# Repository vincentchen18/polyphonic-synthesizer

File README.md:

# Polyphonic Synthesizer

## Overview

You're probably wondering why this is called a polyphonic synthesizer. Well, I thought it sounded fancier than "scrappy 2 octave piano". Anyway, this is my 2nd PCB project, made for the week 3, Instruments, of the [Half Life YSWS](halflife.hackclub.com) from Hack Club.

As a former unskilled piano player (AMEB G6), I decided to make an electronic keyboard this week cos why not. :))) 

Well, at least it's supposed to be an electric keyboard. I'm pretty sure the keys are a bit smaller than they actually are supposed to be, but at least their shape is recognisable, right?

## Schematics

Above is my final schematic for the Synthesizer. As you can see, it contains a USB-C receptacle, Raspberry Pi Pico, some OLEDs, 25 switches (1 per key for 25 keys), and 8 knobs for customised sound settings.

## Hardware and assembly

This is my PCB render of my project. 

Basically, you need a bunch of Cherry MX switches that you need to stick onto the squares at the bottom. 

Then, you gotta 3D print the white and black key files in [here](3D%20Models/STLs/), ideally in PLA or PETG filament. 

Next, you need to stick the holes of the 3D printed parts onto the stems of the switches, and there should be enough tolerance to stick it in easily.

There's also a bunch of soldering that you need to do for the electrical components, but aside from that it's pretty easy.

It is also important to note that the [enclosure](3D%20Models/STLs/enclosure.stl) is completely optional, and exists only to hold the PCB so it doesn't slide around if you're trying to play it. It does not in any way affect the functionality of the actual piano.

If you do print the enclosure, please note that it is too large for a standard 3D printer with a buildspace of 220mm x 220mm x 220mm, so I have already halved the box in the STL model, and all you gotta do is either superglue the halves together or zip tie the 2 halves together using the provided 6mm diameter zip tie holes. (Zip ties are recommended)

The enclosure also has 2 holes for the USB cable and also the audio jack. Place the PCB inside it accordingly. 

You may also notice that there is absolutely no top panel or lid for the enclosure. Please note that this is **intended**. so you can see my beautiful silkscreen art and also I do not have any access to hinges :CC

## Features

I dont even have much to say here, it's just a regular piano?? If you're seeing this and you're a music student then this is a sign to go back to studying music theory.

- Optional Ear/Headphone support (there's an audio jack but you don't need to use it. unfortunately no bluetooth support :C)
- Feels like an actual electronic keyboard (cos of the keyswitches =DDD)
- Adjustable knobs (edit: im done programming firmware! :3)

| Knob | What it does                                                                             |
|---|------------------------------------------------------------------------------------------|
| **Volume** | how loud the thingy is                                                                   |
| **Instrument** | switches between 5 sounds: Piano, Organ, Pluck, Bell and 8-bit                           |
| **Tone** | makes it darker or brighter, like turning the treble down/up                             |
| **Attack** | how fast a note fades in, turn up for a swell similar to a violin                        |
| **Release** | basically a damper pedal                                                                 |
| **Echo** | adds repeating echoes                                                                    |
| **Octave** | shifts the keyboard +/- 2 octaves so you can basically get the range of the entire piano |
| **Transpose** | shifts every note +/- 6 semitones in case you get bored of your key                      |

- The OLED shows the current instrument, octave and transpose, a bar when you turn a knob, and the notes you're holding.

## 3D models

The 3d modelling was made in onshape. Find the editable model at this link: [https://cad.onshape.com/documents/eaea6aaede962270a3775490/w/8b0d608019392835e9ec1b16/e/e5c3a90dd200dcba6fe43490?renderMode=0&uiState=6adddfe965922c75c7df5742](https://cad.onshape.com/documents/eaea6aaede962270a3775490/w/8b0d608019392835e9ec1b16/e/e5c3a90dd200dcba6fe43490?renderMode=0&uiState=6adddfe965922c75c7df5742)

## Firmware

The Firmware for this project is programmed in Arduino IDE.

## AI Usage

No AI used in this project.

## Bill of Materials

### Grant-funded ($30 USD)

| Item | Purpose | Qty | Price | Source |
|---|---|---|---|---|
| Custom PCB 300×90mm, 2-layer (incl. shipping, $5 JLCONE coupon) | Main board | 5 | US$23.25 | [JLCPCB](https://jlcpcb.com) |
| USB-C receptacle HRO TYPE-C-31-M-12 | Power + USB data | 5 | US$0.87 | [LCSC](https://www.lcsc.com/product-detail/C165948.html) |
| SMAJ5.0CA TVS diode | USB ESD protection | 20 | US$0.61 | [LCSC](https://www.lcsc.com/product-detail/C908809.html) |
| SMD1206-050-16 500mA polyfuse | USB overcurrent protection | 10 | US$0.43 | [LCSC](https://www.lcsc.com/product-detail/C46641014.html) |
| Raspberry Pi Pico RP2040 (micro USB) + free knob caps (incl. GST) | Microcontroller | 1 | US$3.16 | [AliExpress](https://www.aliexpress.com/item/1005004565422217.html) |
| **Grant total** | | | **US$28.32** | |

### Paid out of pocket

| Item | Purpose                                                                              | Qty | Price | Source |
|---|--------------------------------------------------------------------------------------|---|---|---|
| Gateron G Pro 3.0 MX switches (30pc) | Keys (25 needed, 8 leftover from [Starbie](https://github.com/vincentchen18/starbie)) | 1 pack | AU$5.49 | [AliExpress](https://www.aliexpress.com/item/1005010559544082.html) |
| 1N4148 DO-35 diodes (50pc) | Key matrix anti-ghosting                                                             | 1 pack | AU$2.83 | [AliExpress](https://www.aliexpress.com/item/1005012020521505.html) |
| RV09 10K vertical potentiometers (5pc) | 8 control knobs                                                                      | 2 packs | AU$2.78 | [AliExpress](https://www.aliexpress.com/item/1871188517.html) |
| CD4051BE DIP-16 | Analog mux for the 8 knobs                                                           | 1 | AU$2.44 | [AliExpress](https://www.aliexpress.com/item/1005012399429493.html) |
| 0.96" I2C OLED 128x64 | Display                                                                              | 1 | AU$3.74 | [AliExpress](https://www.aliexpress.com/item/1005009784993412.html) |
| GY-PCM5102 I2S DAC module | Audio DAC + headphone jack                                                           | 1 | AU$4.19 | [AliExpress](https://www.aliexpress.com/item/1005005692721202.html) |
| PAM8302A CJMCU-832 amp module | Speaker amplifier                                                                    | 1 | AU$2.50 | [AliExpress](https://www.aliexpress.com/item/1005007274382818.html) |
| 8Ω 1W 28mm speaker (2pc) | Speaker                                                                              | 1 pack | AU$4.60 | [AliExpress](https://www.aliexpress.com/item/1005009051447480.html) |
| 10% GST | Tax                                                                                  | — | AU$2.86 | — |
| **Out-of-pocket total** |                                                                                      | | **AU$31.43 (US$21.98)** | |

### Already owned

| Item | Purpose | Qty |
|---|---|---|
| 10k resistors (1/4W) | USB-C CC pull-downs | 4 |

**Project total: US$50.30** *(AUD converted at AU$1 = US$0.6994)*

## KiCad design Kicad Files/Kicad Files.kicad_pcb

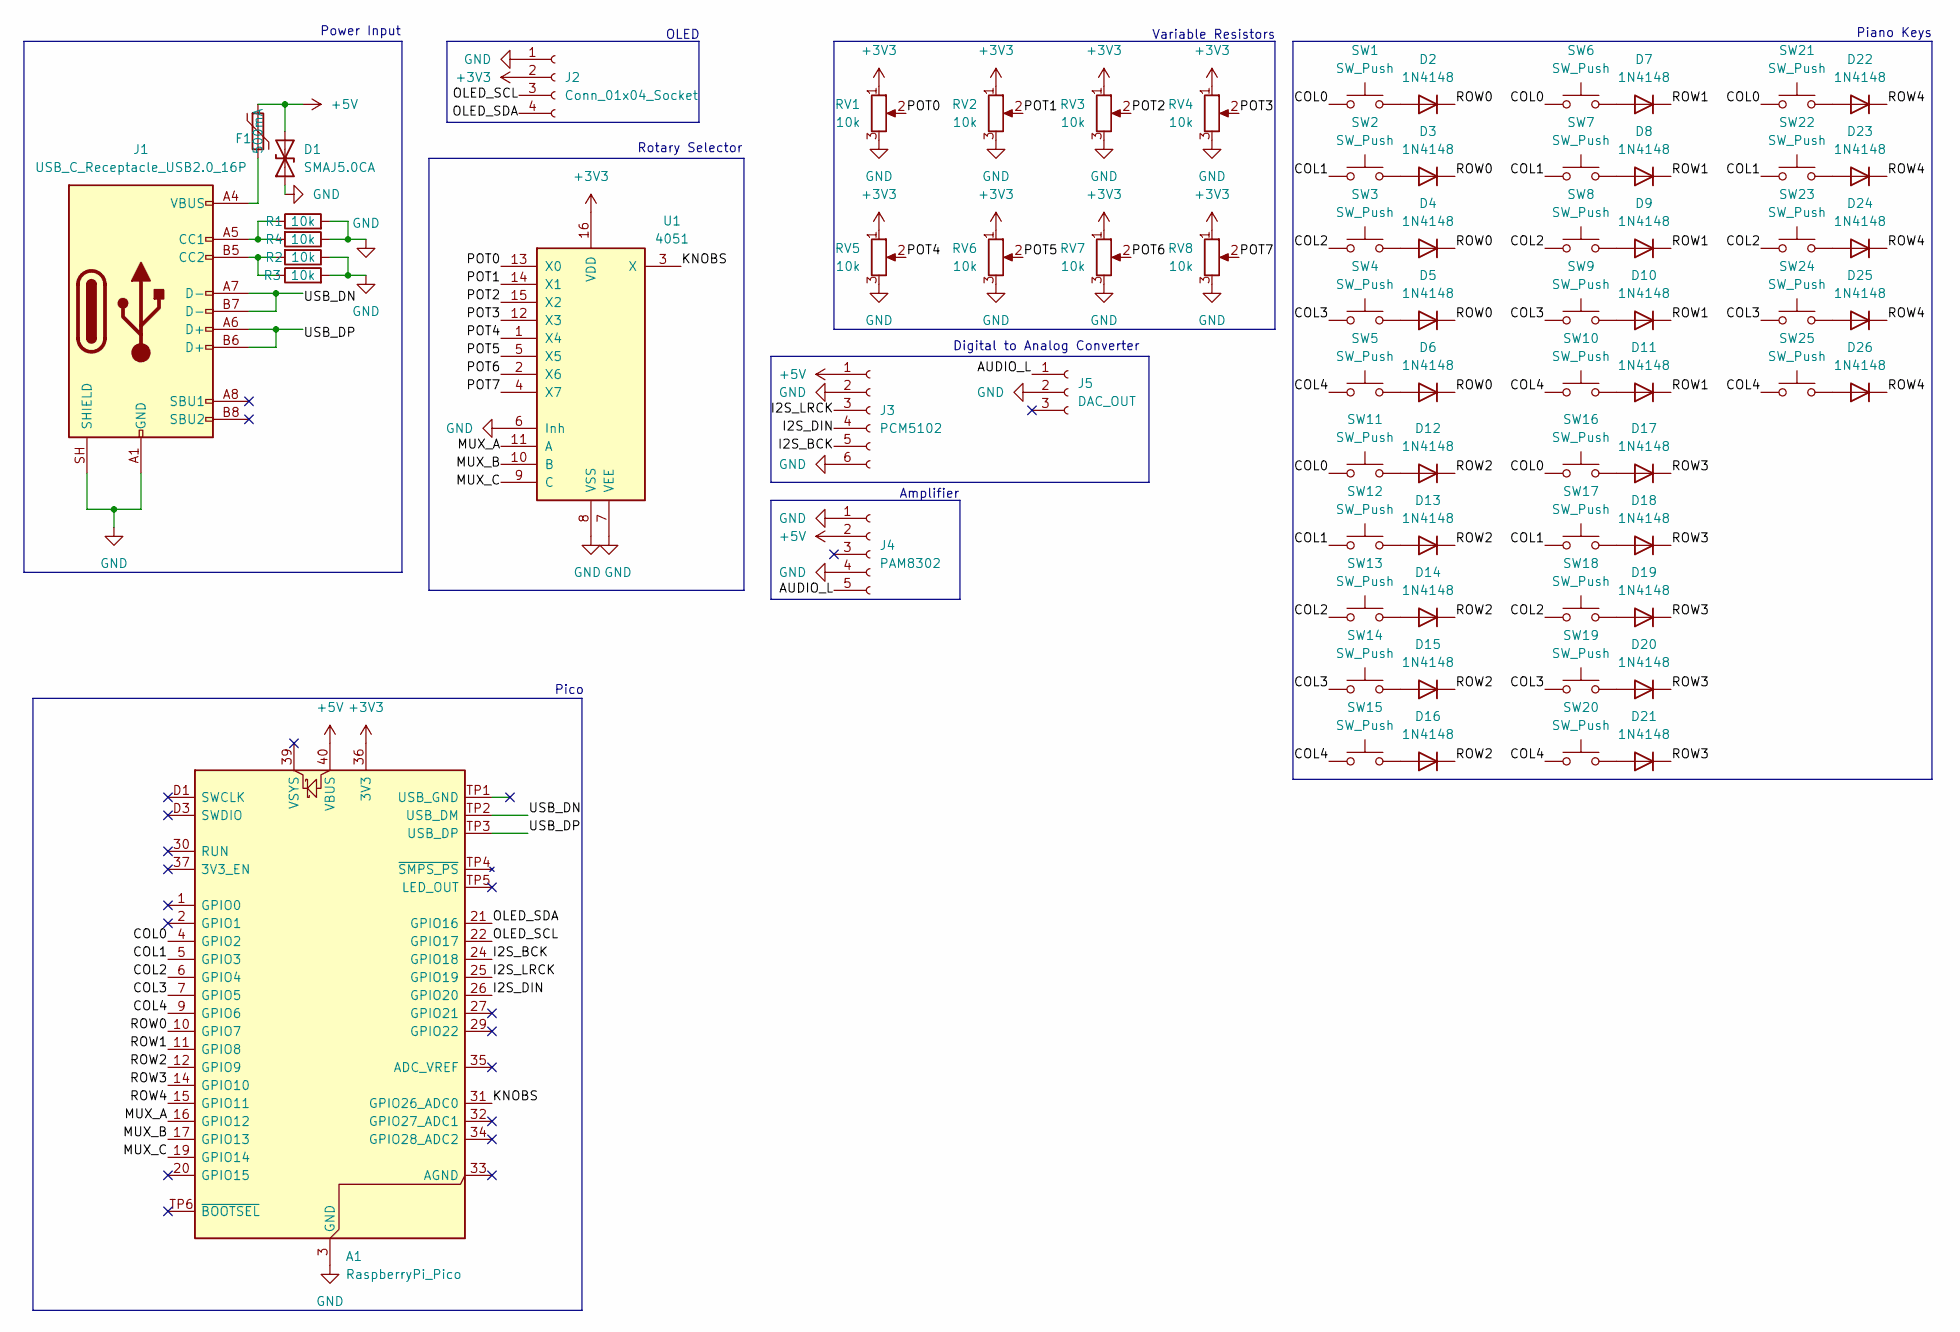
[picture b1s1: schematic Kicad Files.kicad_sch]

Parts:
A1: RaspberryPi_Pico; RaspberryPi_Pico_SMD
D1: SMAJ5.0CA; D_SMA_Handsoldering
D2, D3, D4, D5, D6, D7, D8, D9, D10, D11, D12, D13, D14, D15, D16, D17, D18, D19, D20, D21, D22, D23, D24, D25, D26: 1N4148; D_DO-35_SOD27_P7.62mm_Horizontal
F1: 500mA; Fuse_1206_3216Metric_Pad1.42x1.75mm_HandSolder
J1: USB_C_Receptacle_USB2.0_16P; USB_C_Receptacle_HRO_TYPE-C-31-M-12
J2: Conn_01x04_Socket; PinSocket_1x04_P2.54mm_Vertical
J3: PCM5102; PinSocket_1x06_P2.54mm_Vertical
J4: PAM8302; PinSocket_1x05_P2.54mm_Vertical
J5: DAC_OUT; PinSocket_1x03_P2.54mm_Vertical
R1, R2, R3, R4: 10k; R_Axial_DIN0207_L6.3mm_D2.5mm_P7.62mm_Horizontal
RV1, RV2, RV3, RV4, RV5, RV6, RV7, RV8: 10k; Potentiometer_Alps_RK09K_Single_Vertical
SW1, SW2, SW3, SW4, SW5, SW6, SW7, SW8, SW9, SW10, SW11, SW12, SW13, SW14, SW15, SW16, SW17, SW18, SW19, SW20, SW21, SW22, SW23, SW24, SW25: SW_Push; SW_Cherry_MX_1.00u_PCB
U1: 4051; DIP-16_W7.62mm

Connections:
+3V3: A1.36 (3V3), J2.2, RV1.1, RV2.1, RV3.1, RV4.1, RV5.1, RV6.1, RV7.1, RV8.1, U1.16 (VDD)
+5V: A1.40 (VBUS), D1.2 (A2), F1.1, J3.1, J4.2
/AUDIO_L: J4.5, J5.1
/COL0: A1.4 (GPIO2), SW1.1, SW6.1, SW11.1, SW16.1, SW21.1
/COL1: A1.5 (GPIO3), SW2.1, SW7.1, SW12.1, SW17.1, SW22.1
/COL2: A1.6 (GPIO4), SW3.1, SW8.1, SW13.1, SW18.1, SW23.1
/COL3: A1.7 (GPIO5), SW4.1, SW9.1, SW14.1, SW19.1, SW24.1
/COL4: A1.9 (GPIO6), SW5.1, SW10.1, SW15.1, SW20.1, SW25.1
/I2S_BCK: A1.24 (GPIO18), J3.5
/I2S_DIN: A1.26 (GPIO20), J3.4
/I2S_LRCK: A1.25 (GPIO19), J3.3
/KNOBS: A1.31 (GPIO26_ADC0), U1.3 (X)
/MUX_A: A1.16 (GPIO12), U1.11 (A)
/MUX_B: A1.17 (GPIO13), U1.10 (B)
/MUX_C: A1.19 (GPIO14), U1.9 (C)
/OLED_SCL: A1.22 (GPIO17), J2.3
/OLED_SDA: A1.21 (GPIO16), J2.4
/POT0: RV1.2, U1.13 (X0)
/POT1: RV2.2, U1.14 (X1)
/POT2: RV3.2, U1.15 (X2)
/POT3: RV4.2, U1.12 (X3)
/POT4: RV5.2, U1.1 (X4)
/POT5: RV6.2, U1.5 (X5)
/POT6: RV7.2, U1.2 (X6)
/POT7: RV8.2, U1.4 (X7)
/ROW0: A1.10 (GPIO7), D2.1 (K), D3.1 (K), D4.1 (K), D5.1 (K), D6.1 (K)
/ROW1: A1.11 (GPIO8), D7.1 (K), D8.1 (K), D9.1 (K), D10.1 (K), D11.1 (K)
/ROW2: A1.12 (GPIO9), D12.1 (K), D13.1 (K), D14.1 (K), D15.1 (K), D16.1 (K)
/ROW3: A1.14 (GPIO10), D17.1 (K), D18.1 (K), D19.1 (K), D20.1 (K), D21.1 (K)
/ROW4: A1.15 (GPIO11), D22.1 (K), D23.1 (K), D24.1 (K), D25.1 (K), D26.1 (K)
/USB_DN: A1.TP2 (USB_DM), J1.A7 (D-), J1.B7 (D-)
/USB_DP: A1.TP3 (USB_DP), J1.A6 (D+), J1.B6 (D+)
GND: A1.3 (GND), A1.8 (GND), A1.13 (GND), A1.18 (GND), A1.23 (GND), A1.28 (GND), A1.38 (GND), A1.D2 (GND), D1.1 (A1), J1.A1 (GND), J1.A12 (GND), J1.B1 (GND), J1.B12 (GND), J1.SH (SHIELD), J2.1, J3.2, J3.6, J4.1, J4.4, J5.2, R1.2, R2.1, R3.2, R4.1, RV1.3, RV2.3, RV3.3, RV4.3, RV5.3, RV6.3, RV7.3, RV8.3, U1.6 (Inh), U1.7 (VEE), U1.8 (VSS)
unnamed: D2.2 (A), SW1.2
unnamed: D3.2 (A), SW2.2
unnamed: D4.2 (A), SW3.2
unnamed: D5.2 (A), SW4.2
unnamed: D6.2 (A), SW5.2
unnamed: D7.2 (A), SW6.2
unnamed: D8.2 (A), SW7.2
unnamed: D9.2 (A), SW8.2
unnamed: D10.2 (A), SW9.2
unnamed: D11.2 (A), SW10.2
unnamed: D12.2 (A), SW11.2
unnamed: D13.2 (A), SW12.2
unnamed: D14.2 (A), SW13.2
unnamed: D15.2 (A), SW14.2
unnamed: D16.2 (A), SW15.2
unnamed: D17.2 (A), SW16.2
unnamed: D18.2 (A), SW17.2
unnamed: D19.2 (A), SW18.2
unnamed: D20.2 (A), SW19.2
unnamed: D21.2 (A), SW20.2
unnamed: D22.2 (A), SW21.2
unnamed: D23.2 (A), SW22.2
unnamed: D24.2 (A), SW23.2
unnamed: D25.2 (A), SW24.2
unnamed: D26.2 (A), SW25.2
unnamed: F1.2, J1.A4 (VBUS), J1.A9 (VBUS), J1.B4 (VBUS), J1.B9 (VBUS)
unnamed: J1.A5 (CC1), R1.1, R4.2
unnamed: J1.B5 (CC2), R2.2, R3.1

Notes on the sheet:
Piano Keys
Amplifier
Digital to Analog Converter
Rotary Selector
Pico
Variable Resistors
OLED
Power Input

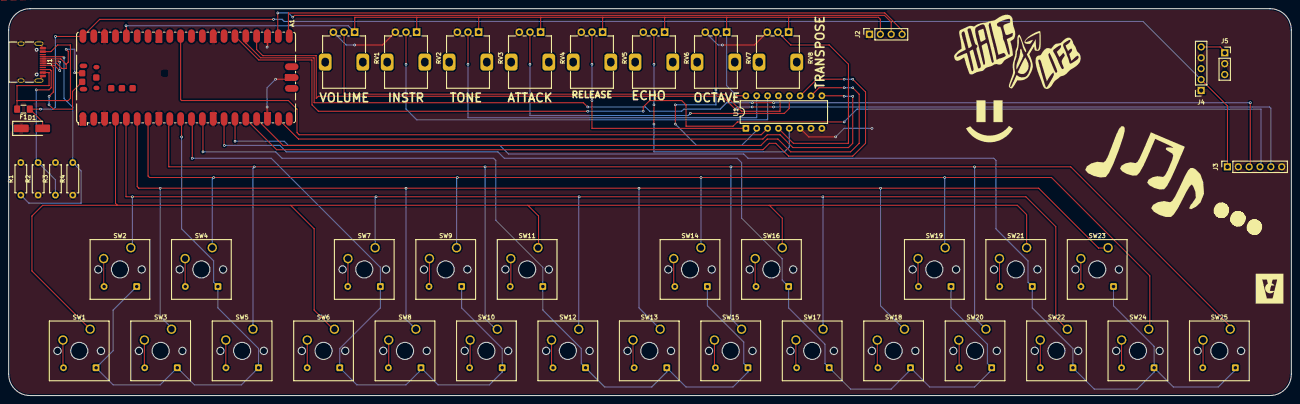
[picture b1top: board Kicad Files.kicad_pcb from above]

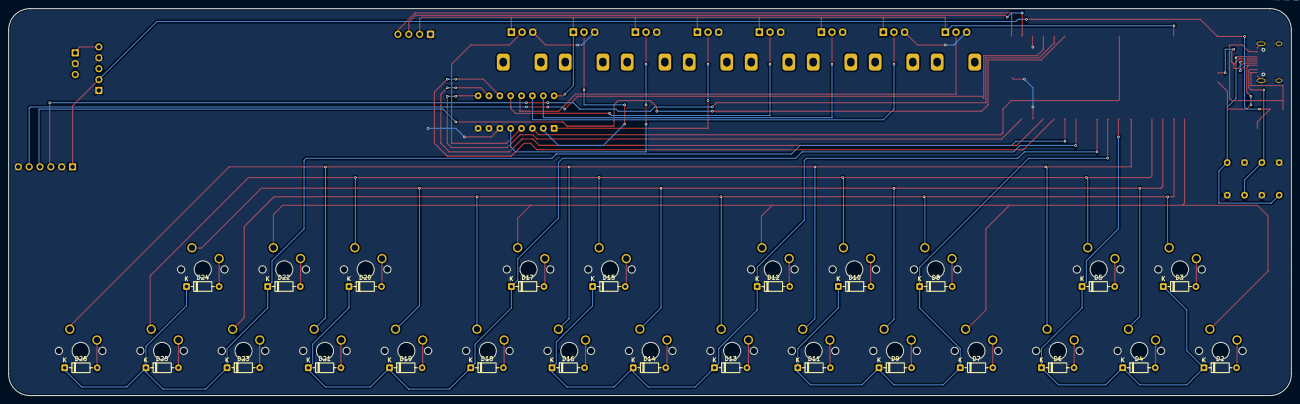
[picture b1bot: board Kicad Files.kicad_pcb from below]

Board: 2 copper layers, 300.1 x 90.5 mm, 71 parts (25 on the bottom side), 61 nets.

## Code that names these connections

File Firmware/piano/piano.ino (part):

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const uint8_t MUX_PINS[3] = {12, 13, 14};
const uint8_t KNOB_PIN = 26;
// not keys anymore but still pins
const uint8_t OLED_SDA = 16;
const uint8_t OLED_SCL = 17;
const uint8_t I2S_BCK = 18;
const uint8_t I2S_DIN = 20; 

// keys

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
